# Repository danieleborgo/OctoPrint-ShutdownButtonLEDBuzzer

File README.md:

# ShutdownButtonLEDBuzzer

This OctoPrint plugin implements a shutdown physical button
for the Raspberry Pi. It offers also a status LED to know when
OctoPrint is ready and a buzzer to signal the startup and
the shutdown. Remember that these signals may vary of few
seconds.

By default, this plugin shuts down the Raspberry without
checking of there are ongoing jobs. In settings, there is
a flag to disable the button when printing.

## Compatibility

The plugin automatically selects the correct GPIO driver based on
the OS version:

- **periphery** — for Raspberry Pi OS **Bookworm (2023) and newer**,
  including Raspberry Pi 5. Uses the modern character device interface
  (`/dev/gpiochip0`, or `/dev/gpiochip4` on Raspberry Pi 5).
- **gpiozero** — for Raspberry Pi OS **Bullseye (2021) and older**.
  Requires the legacy sysfs interface.

Auto-detection is the default and works in most cases. If needed,
the driver can be overridden in the Advanced Settings section.

`python-periphery` is a required dependency. `gpiozero` is optional
and only needed on older systems:

    pip install "OctoPrint-ShutdownButtonLEDBuzzer[gpiozero]"

## Notes

To shut down the Raspberry, it uses the command configured in
OctoPrint settings.

This plugin supports both active and passive buzzers. By default,
it assumes to have an active one.

The internal pull-up resistor for the button is applied automatically
on kernels ≥ 5.10. On older kernels an external pull-up resistor
on the button pin is required.

## Setup

Install via the bundled 
[Plugin Manager](
https://docs.octoprint.org/en/master/bundledplugins/pluginmanager.html)
or manually using this URL:

    https://github.com/danieleborgo/OctoPrint-ShutdownButtonLEDBuzzer/archive/master.zip

## Circuit

The circuit hereafter exposed is just the one set by default,
since the plugin allows to edit each of these pin:

- Button: by default directly on pin GPIO26
- LED: by default on pin GPIO6
- Buzzer: by default on pin GPIO13

In case one of these features is not needed, it can be
deactivated by the apposite settings section.

Always remember to properly check each connection, using
the official datasheet, before turning on the Raspberry.

## Configuration

This plugin offers several configuration parameters,
accessible in the apposite OctoPrint section in setting:

## PCB

There are KiCad PCB files available in case you want to make your own PCB.
A bill of materials (BOM) can be found in the according folder.

## FAQ

#### _What resistor does it need to use?_ 

There is no a precise resistor needed, since it depends on how much
light is needed. Despite this, it is suggested to use a value at
least of few thousands of ohms. Always remember to check the 
connections and the datasheet.

#### _Which buzzer does it need?_

The plugin supports both active that passive buzzer, but it is
necessary to configure them by the settings panel.

#### Which LED does it need?

A 5 mm LED is a good option, and it is usually in Arduino kits.
In case a different one is attached, check that the current it needs
is lower than the one a Raspberry pin can give.

## License

This software is distributed on GPLv3.0, more information
available in [LICENSE.md](
https://github.com/danieleborgo/OctoPrint-ShutdownButtonLEDBuzzer/blob/master/LICENSE.md).

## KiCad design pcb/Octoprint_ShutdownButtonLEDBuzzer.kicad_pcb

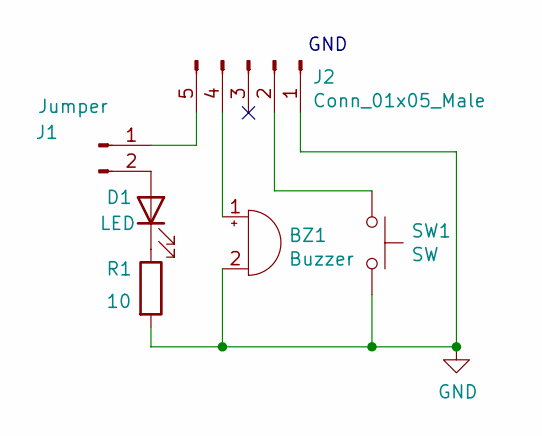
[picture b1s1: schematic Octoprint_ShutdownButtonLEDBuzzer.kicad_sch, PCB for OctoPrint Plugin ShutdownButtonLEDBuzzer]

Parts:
BZ1: Buzzer; Buzzer_12x9.5RM7.6
D1: LED; LED_D5.0mm
J1: Jumper; PinHeader_1x02_P2.54mm_Vertical
J2: Conn_01x05_Male; PinHeader_1x05_P2.54mm_Vertical
R1: 10; R_Axial_DIN0207_L6.3mm_D2.5mm_P7.62mm_Horizontal
SW1: SW; SW_Tactile_Straight_KSA0Axx1LFTR

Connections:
GND: BZ1.2 (+), J2.1, R1.2, SW1.2
unnamed: BZ1.1 (-), J2.4
unnamed: D1.1 (K), R1.1
unnamed: D1.2 (A), J1.2
unnamed: J1.1, J2.5
unnamed: J2.2, SW1.1

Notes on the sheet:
GND

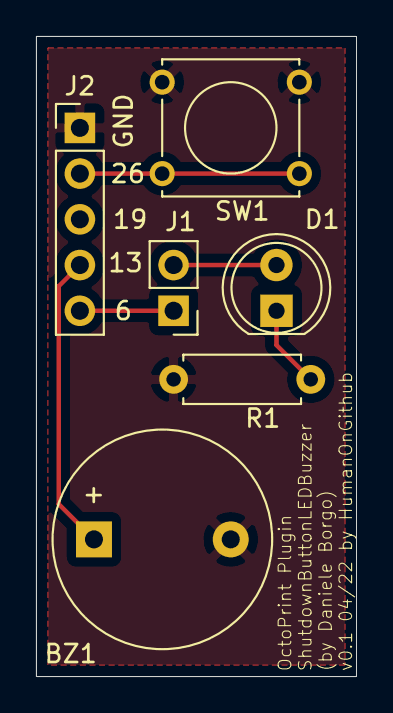
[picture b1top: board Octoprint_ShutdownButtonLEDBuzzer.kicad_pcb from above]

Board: 2 copper layers, 17.8 x 35.6 mm, 6 parts (0 on the bottom side), 6 nets.

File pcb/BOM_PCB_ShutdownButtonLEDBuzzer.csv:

BOM PCB ShutdownButtonLEDBuzzer;;;;;
;;;;;
;;;;;
Amount;Description;Single price;Price;Link;Position
1;VIS 3590 12 mm Magnetischer Buzzer;2,25 ; 2,25  ;https://www.reichelt.de/12-mm-magnetischer-buzzer-vis-3590-p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;BZ1
1;Widerstand 10 Ohm;0,15 ; 0,15  ;https://www.reichelt.de/widerstand-metalloxyd-10-ohm-0207-1-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;R1
1;LED grün;0,08 ; 0,08  ;https://www.reichelt.de/led-5-mm-bedrahtet-gruen-fr-led-5-gr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;D1
1;MPE 087-1-002 Stiftleisten 2,54 mm, 1X02, gerade;0,06 ; 0,06  ;https://www.reichelt.de/stiftleisten-2-54-mm-1x02-gerade-mpe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;J1
1;JUMPER 2,54 SW Kurzschlussbrücke, schwarz, RM 2,54;0,03 ; 0,03  ;https://www.reichelt.de/kurzschlussbruecke-schwarz-rm-2-54-j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;J1
1;TASTER 3301B Kurzhubtaster 6x6mm, Höhe: 9,5mm, 12V, vertikal;0,20 ; 0,20  ;https://www.reichelt.de/kurzhubtaster-6x6mm-hoehe-4-3mm-12v-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;SW1
1;PSK 254/5W Kupplungs-Leergehäuse, Crimptechnik, 5-polig;0,03 ; 0,03  ;https://www.reichelt.de/kupplungs-leergehaeuse-crimptechnik-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;J2
1;PSS 254/5G Printstecker, Einzelstecker, gerade, 5-polig;0,09 ; 0,09  ;https://www.reichelt.de/printstecker-einzelstecker-gerade-5-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;J2
1;PSK-KONTAKTE Crimpkontakte für psk 254;0,24 ; 0,24  ;https://www.reichelt.de/crimpkontakte-fuer-psk-254--20-stuec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;
1;BL 1X10G8 2,54 10pol. Buchsenleiste, gerade, RM 2,54, H: 8,5mm;0,22 ; 0,22  ;https://www.reichelt.de/10pol-buchsenleiste-gerade-rm-2-54-h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;J2
;;SUM; 3,35  ;;

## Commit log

2021-12-10 Implemented the first version: - Shutdown button - Status LED - Buzzer
2021-12-12 Licensed and completed README.md
2021-12-15 Implemented the possibility to check I2C and SPI state from setting
2021-12-15 Implemented last updated for refresh
2021-12-20 - Avoided locks due to the buzzer with a thread pool - Bug fix on multiple shutdown invocation - Changed GET request with POST - Bug fix on numeric values in settings
2021-12-22 Added the circuit
2022-01-02 Bug fix on shutdown beeps
2022-01-09 Updated setup.py
2022-01-14 Corrected a typo
2022-01-17 Minor fixes
2022-01-18 Fully moved to gpiozero
2022-02-03 - Passive buzzers are now supported - Code optimization - Added FAQs - Updated circuit image
2022-02-12 Does not shutdown on octopi image, on pi 3 b, since the image uses sudo to execute shutdown command.
2022-02-22 Added sudo to the shutdown command
2022-02-24 The plugin now uses OctoPrint's shutdown command
2022-05-30 Implemented the possibility to disable the button in case of printing
2023-02-12 extend project with kiCad-pcb files
2023-02-12 readme edited with PCB information
2026-04-10 Add multi-driver GPIO abstraction and fix Bookworm compatibility: - Introduce manager package with AbstractGPIOManager, GpiozeroGPIOManager and PeripheryGPIOManager; auto-select periphery on Debian 1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
